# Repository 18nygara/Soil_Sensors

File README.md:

# Soil_Sensors

Soil Sensing and Monitoring project for Hendri Winanto's Master's Thesis and Professor Jingyi Huang - UW Madison.

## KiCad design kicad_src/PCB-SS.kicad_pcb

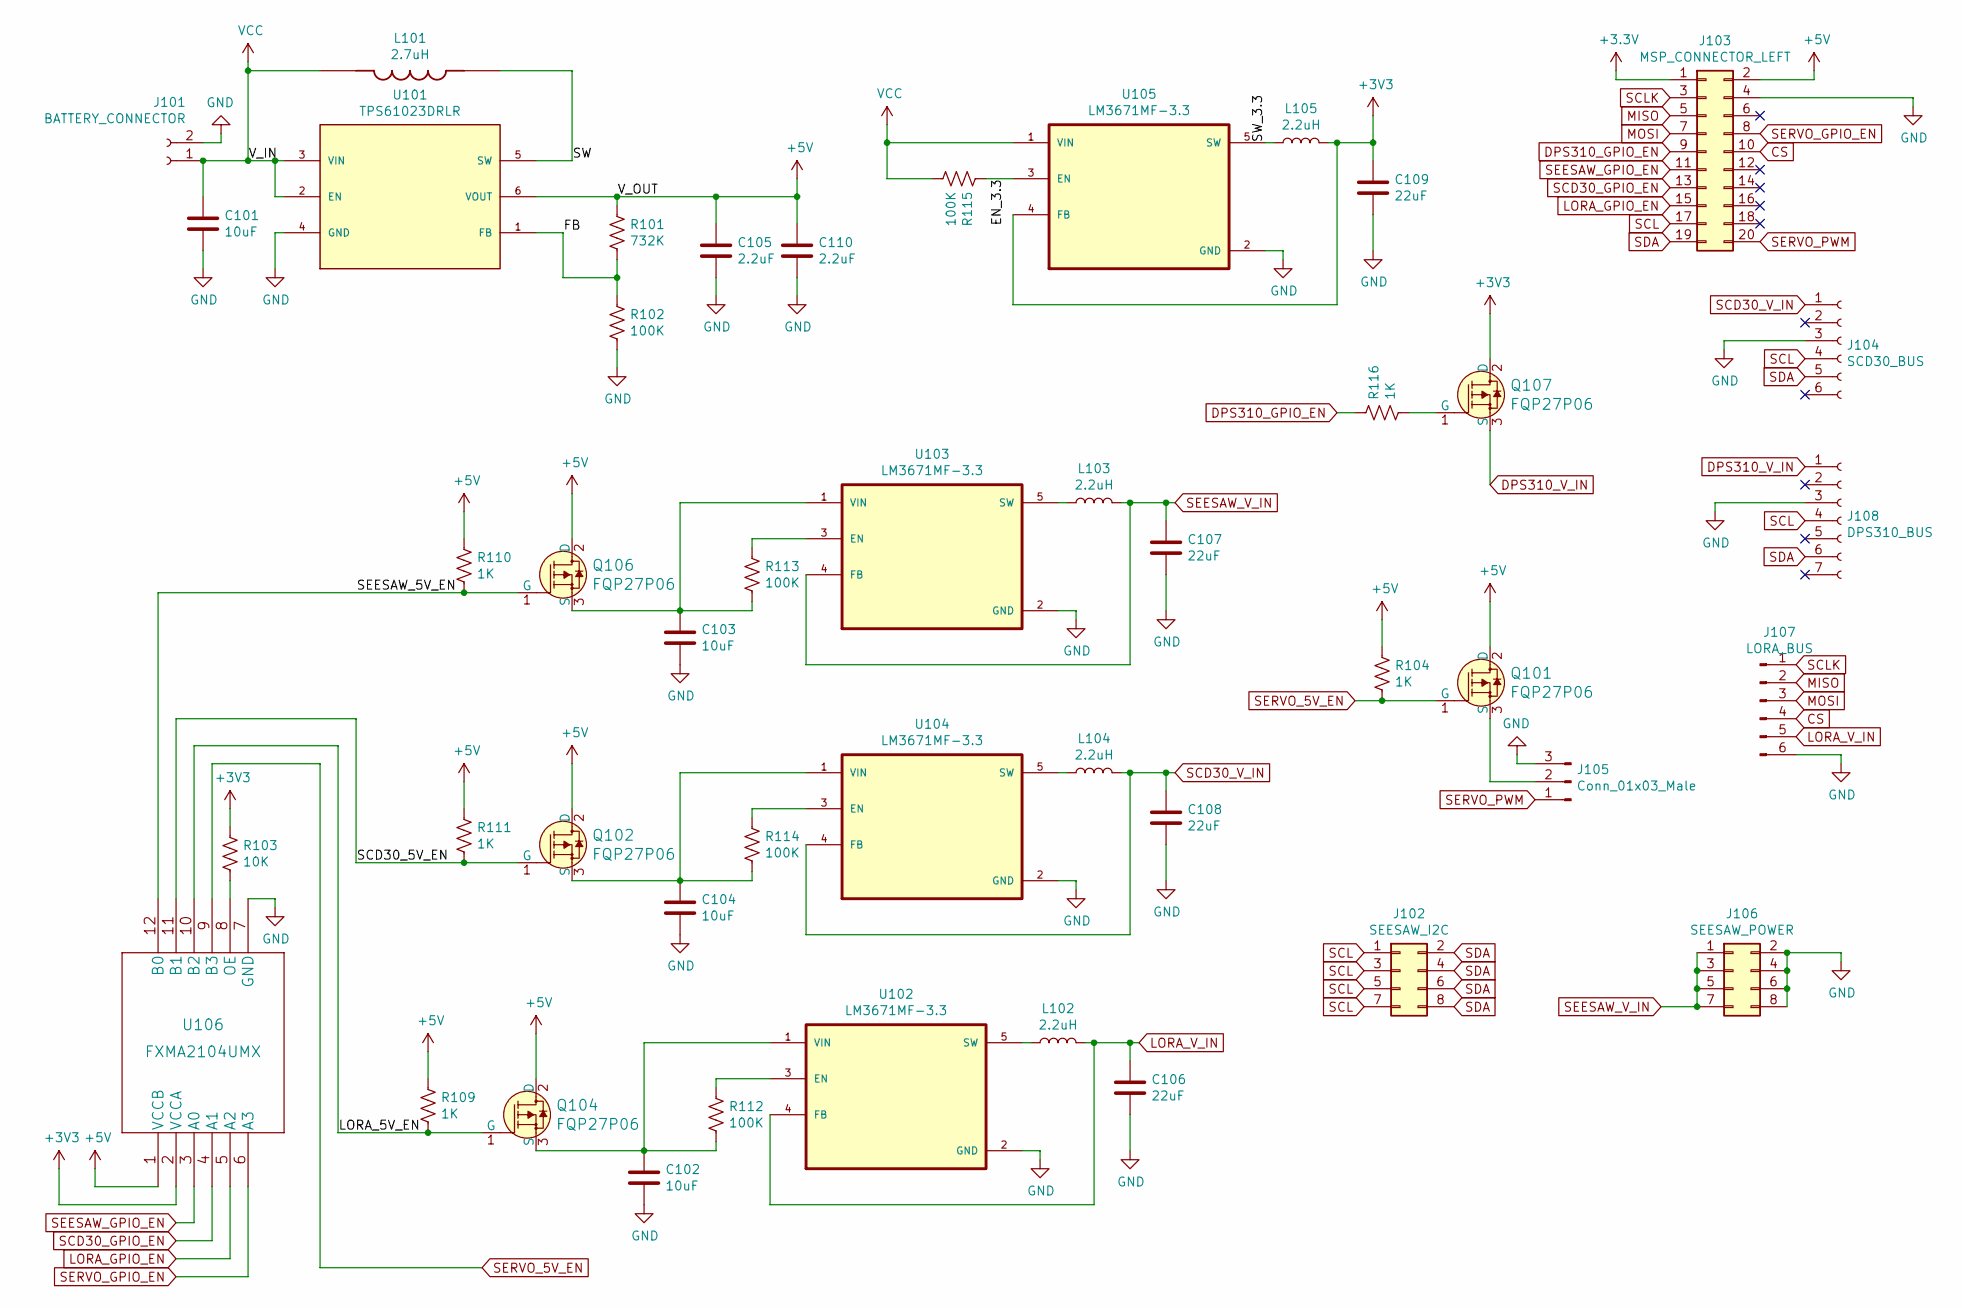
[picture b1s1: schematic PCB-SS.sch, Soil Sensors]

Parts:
C101, C102, C103, C104: 10uF; C_0805_2012Metric
C105, C110: 2.2uF; C_0402_1005Metric
C106, C107, C108, C109: 22uF; C_0805_2012Metric
J101: BATTERY_CONNECTOR; JST_PH_S2B-PH-K_1x02_P2.00mm_Horizontal
J102: SEESAW_I2C; PinHeader_2x04_P2.54mm_Vertical
J103: MSP_CONNECTOR_LEFT; PinHeader_2x10_P2.54mm_Vertical
J104: SCD30_BUS; PinSocket_1x06_P2.54mm_Vertical
J105: Conn_01x03_Male; PinHeader_1x03_P2.54mm_Vertical
J106: SEESAW_POWER; PinHeader_2x04_P2.54mm_Vertical
J107: LORA_BUS; PinHeader_1x06_P2.54mm_Vertical
J108: DPS310_BUS; PinSocket_1x07_P2.54mm_Vertical
L101: 2.7uH; IND_1255AY-2R7N=P3; PARTREV N/A
L102, L103, L104, L105: 2.2uH; NRH2412T2R2MNGH
Q101, Q102, Q104, Q106, Q107: FQP27P06; TO-220-3; MPN FQP27P06; Digi-Key_PN FQP27P06-ND
R101: 732K; R_0402_1005Metric
R102, R112, R113, R114, R115: 100K; R_0805_2012Metric
R103: 10K; R_0805_2012Metric
R104, R109, R110, R111, R116: 1K; R_0805_2012Metric
U101: TPS61023DRLR; DRL0006A; PARTNUMBER TPS61023DRL
U102, U103, U104, U105: LM3671MF-3.3; SOT95P280X145-5N
U106: FXMA2104UMX

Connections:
+5V: C105.1, C110.1, J103.2, Q101.2 (D), Q102.2 (D), Q104.2 (D), Q106.2 (D), R101.1, R104.1, R109.1, R110.1, R111.1, U101.6 (VOUT), U106.1 (VCCB)
/EN_3.3: R115.1, U105.3 (EN)
/FB: R101.2, R102.1, U101.1 (FB)
/LORA_5V_EN: Q104.1 (G), R109.2, U106.10 (B2)
/SCD30_5V_EN: Q102.1 (G), R111.2, U106.11 (B1)
/SEESAW_5V_EN: Q106.1 (G), R110.2, U106.12 (B0)
/SW: L101.2, U101.5 (SW)
/SW_3.3: L105.1, U105.5 (SW)
CS: J103.10, J107.4
DPS310_GPIO_EN: J103.9, R116.1
DPS310_V_IN: J108.1, Q107.3 (S)
GND: C101.2, C102.2, C103.2, C104.2, C105.2, C106.2, C107.2, C108.2, C109.2, C110.2, J101.2, J103.4, J104.3, J105.3, J106.2, J106.4, J106.6, J106.8, J107.6, J108.3, R102.2, U101.4 (GND), U102.2 (GND), U103.2 (GND), U104.2 (GND), U105.2 (GND), U106.7 (GND)
LORA_GPIO_EN: J103.15, U106.5 (A2)
LORA_V_IN: C106.1, J107.5, L102.2, U102.4 (FB)
MISO: J103.5, J107.2
MOSI: J103.7, J107.3
unnamed: C102.1, Q104.3 (S), R112.2, U102.1 (VIN)
unnamed: C103.1, Q106.3 (S), R113.2, U103.1 (VIN)
unnamed: C104.1, Q102.3 (S), R114.2, U104.1 (VIN)
unnamed: J105.2, Q101.3 (S)
unnamed: L102.1, U102.5 (SW)
unnamed: L103.1, U103.5 (SW)
unnamed: L104.1, U104.5 (SW)
unnamed: Q107.1 (G), R116.2
unnamed: R103.2, U106.8 (OE)
unnamed: R112.1, U102.3 (EN)
unnamed: R113.1, U103.3 (EN)
unnamed: R114.1, U104.3 (EN)
SCD30_GPIO_EN: J103.13, U106.4 (A1)
SCD30_V_IN: C108.1, J104.1, L104.2, U104.4 (FB)
SCL: J102.1, J102.3, J102.5, J102.7, J103.17, J104.4, J108.4
SCLK: J103.3, J107.1
SDA: J102.2, J102.4, J102.6, J102.8, J103.19, J104.5, J108.6
SEESAW_GPIO_EN: J103.11, U106.3 (A0)
SEESAW_V_IN: C107.1, J106.1, J106.3, J106.5, J106.7, L103.2, U103.4 (FB)
SERVO_5V_EN: Q101.1 (G), R104.2, U106.9 (B3)
SERVO_GPIO_EN: J103.8, U106.6 (A3)
SERVO_PWM: J103.20, J105.1
VCC: C101.1, J101.1, L101.1, R115.2, U101.2 (EN), U101.3 (VIN), U105.1 (VIN)

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
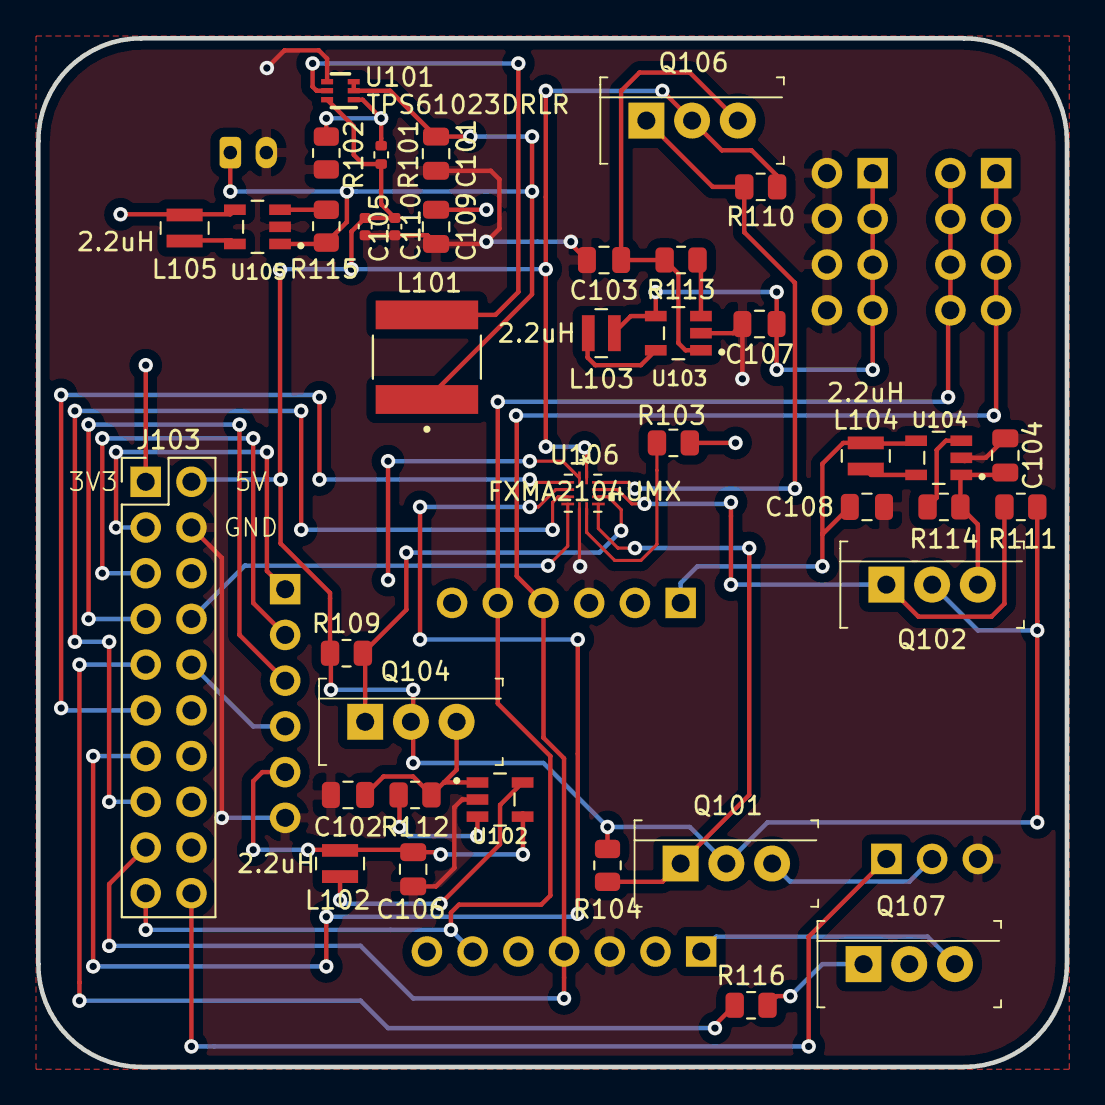
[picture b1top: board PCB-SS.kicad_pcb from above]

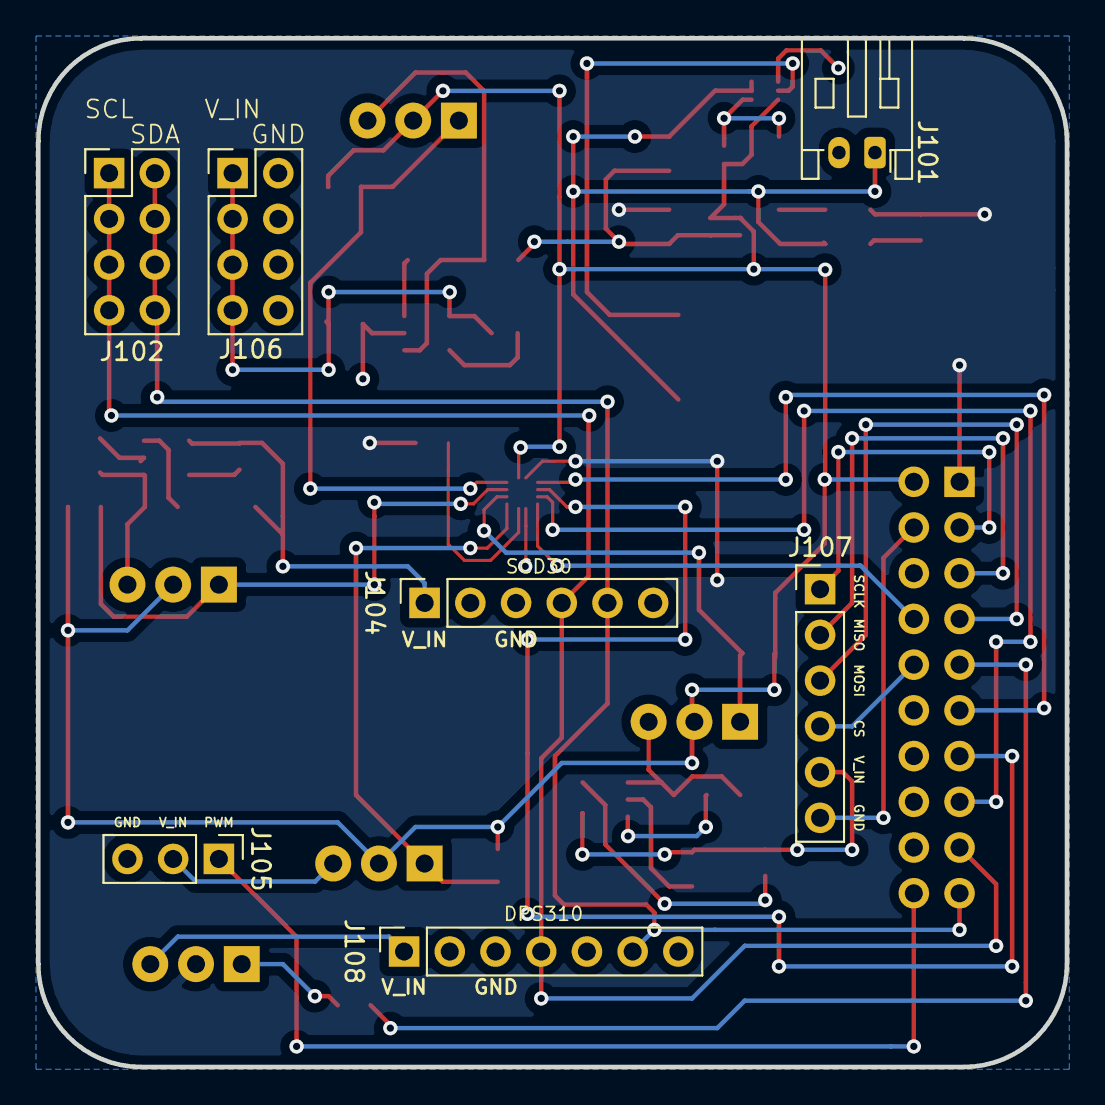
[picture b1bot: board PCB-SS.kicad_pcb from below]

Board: 2 copper layers, 57.2 x 57.2 mm, 46 parts (7 on the bottom side), 40 nets.

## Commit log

2021-11-10 Add arduino and MSP code
2022-01-07 Add KiCAD files
2022-01-16 Update PCB

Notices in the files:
parts and their libraries:
Copyright 2021 Accelerated Designs. All rights reserved.
